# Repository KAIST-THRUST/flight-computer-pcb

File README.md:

# Flight Computer PCB

This repository contains the flight computer PCB design for TU-3 rocket avionics.

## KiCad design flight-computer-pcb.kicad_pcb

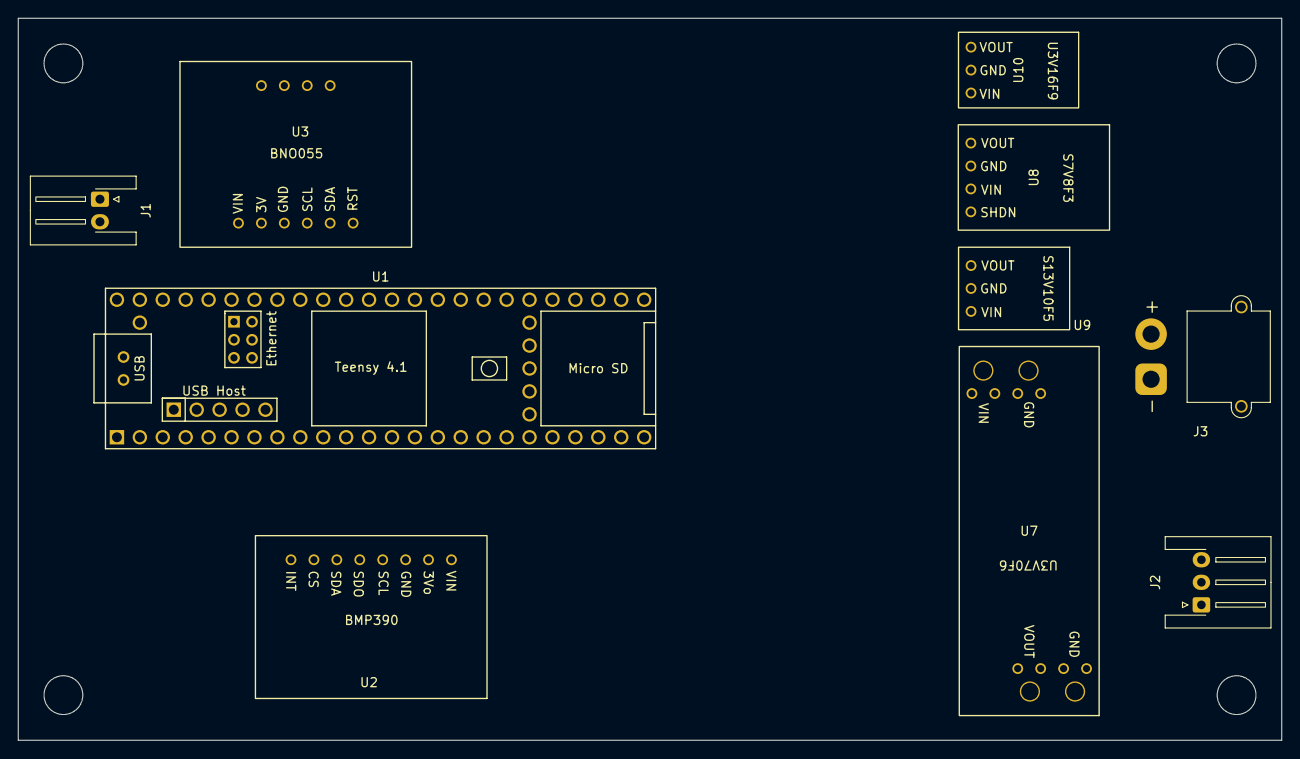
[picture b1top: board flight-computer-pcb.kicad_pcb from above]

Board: 4 copper layers, 140.0 x 80.0 mm, 10 parts (0 on the bottom side), 14 nets, no tracks yet.

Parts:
J1: Conn_02x01; JST_XH_S2B-XH-A-1_1x02_P2.50mm_Horizontal
J2: Conn_01x03; JST_XH_S3B-XH-A-1_1x03_P2.50mm_Horizontal
J3: Conn_02x01; AMASS_XT30PW-M_1x02_P2.50mm_Horizontal
U1: Teensy4.1; Teensy41
U2: BMP390
U3: BNO055
U7: U3V70F6
U8: S7V8F3
U9: S13V10F5
U10: U3V16F9

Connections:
+3.3V: U2.1 (VIN), U3.1 (VIN), U8.1 (Vout)
+5V: U1.48 (VIN), U9.1 (Vout)
+6V: J2.2, U7.1 (Vout)
+9V: J1.1, U10.1 (Vout)
/BMP390_CS: U1.2 (0_RX1_CRX2_CS1), U2.7 (CS)
/BMP390_MISO: U1.3 (1_TX1_CTX2_MISO1), U2.5 (SDO)
/BMP390_MOSI: U1.18 (26_A12_MOSI1), U2.6 (SDA)
/BMP390_SCK: U1.19 (27_A13_SCK1), U2.4 (SCL)
/BNO055_SCL: U1.41 (19_A5_SCL), U3.4 (SCL)
/BNO055_SDA: U1.40 (18_A4_SDA), U3.5 (SDA)
/PT_analog: J1.2, U1.17 (25_A11_RX6_SDA2)
/Servo_PWM: J2.1, U1.4 (2_OUT2)
/VBAT: J3.2, U7.3 (Vin), U8.3 (Vin), U9.3 (Vin), U10.3 (Vin)
GND: J2.3, J3.1, U1.1 (GND), U1.34 (GND), U2.3 (GND), U3.3 (GND), U7.2 (GND), U7.4 (GND), U8.2 (GND), U9.2 (GND), U10.2 (GND)

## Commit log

2026-02-02 feat: initial commit
2026-02-02 feat: add GND layer
2026-02-02 feat: add S13V10F5
2026-02-02 feat: add courtyard to Teensy 4.1 footprint
2026-02-02 feat: add connectors to schematic
2026-02-03 fix: adjust silkscreen line width to 0.15mm
2026-02-03 docs: add "external module" comments to schematic
2026-02-07 feat: add 3d model to S13V10F5
2026-02-07 feat: add basic board setting
2026-02-07 fix: remove silkscreen lines under 0.15mm width
2026-02-09 regulator library added
    regulator library added
    (S7V8F3, U3V16F9, U3V70F6)
    라이브러리에 있는 FlightComputer.kicad_sym와 Teensy.kicad_sym가 열릴 때 오류 메시지가 떠서 좀 건드렸는데 여전히 뭐가 된 건지 안 된 건지 알 수가 없습니다. 현재 오류 메시지는 안 뜨지만 여전히 심볼 없이 그냥 빈 화면만 뜹니다.
2026-02-09 fix: revert Teensy footprint library name
2026-02-09 feat: adjust size and add 3d models to footprints
2026-02-09 feat: add S7V8F3, U3V16F9, and U3V70F6 footprint (#1)
    * add regulator footprint to library
    * fix: revert Teensy footprint library name
    * feat: adjust size and add 3d models to footprints
    ---------
2026-02-09 feat: add S7V8F3, U3V16F9, and U3V70F6 footprint to sch and pcb
2026-02-09 fix: adjust hole spacing in U3V70F6
2026-02-09 fix: delete text size under 0.15mm in Teensy 4.1 footprint
2026-02-10 feat: add M4 mounting holes
2026-02-13 feat: add connector footprints to J1, J2 and J3
